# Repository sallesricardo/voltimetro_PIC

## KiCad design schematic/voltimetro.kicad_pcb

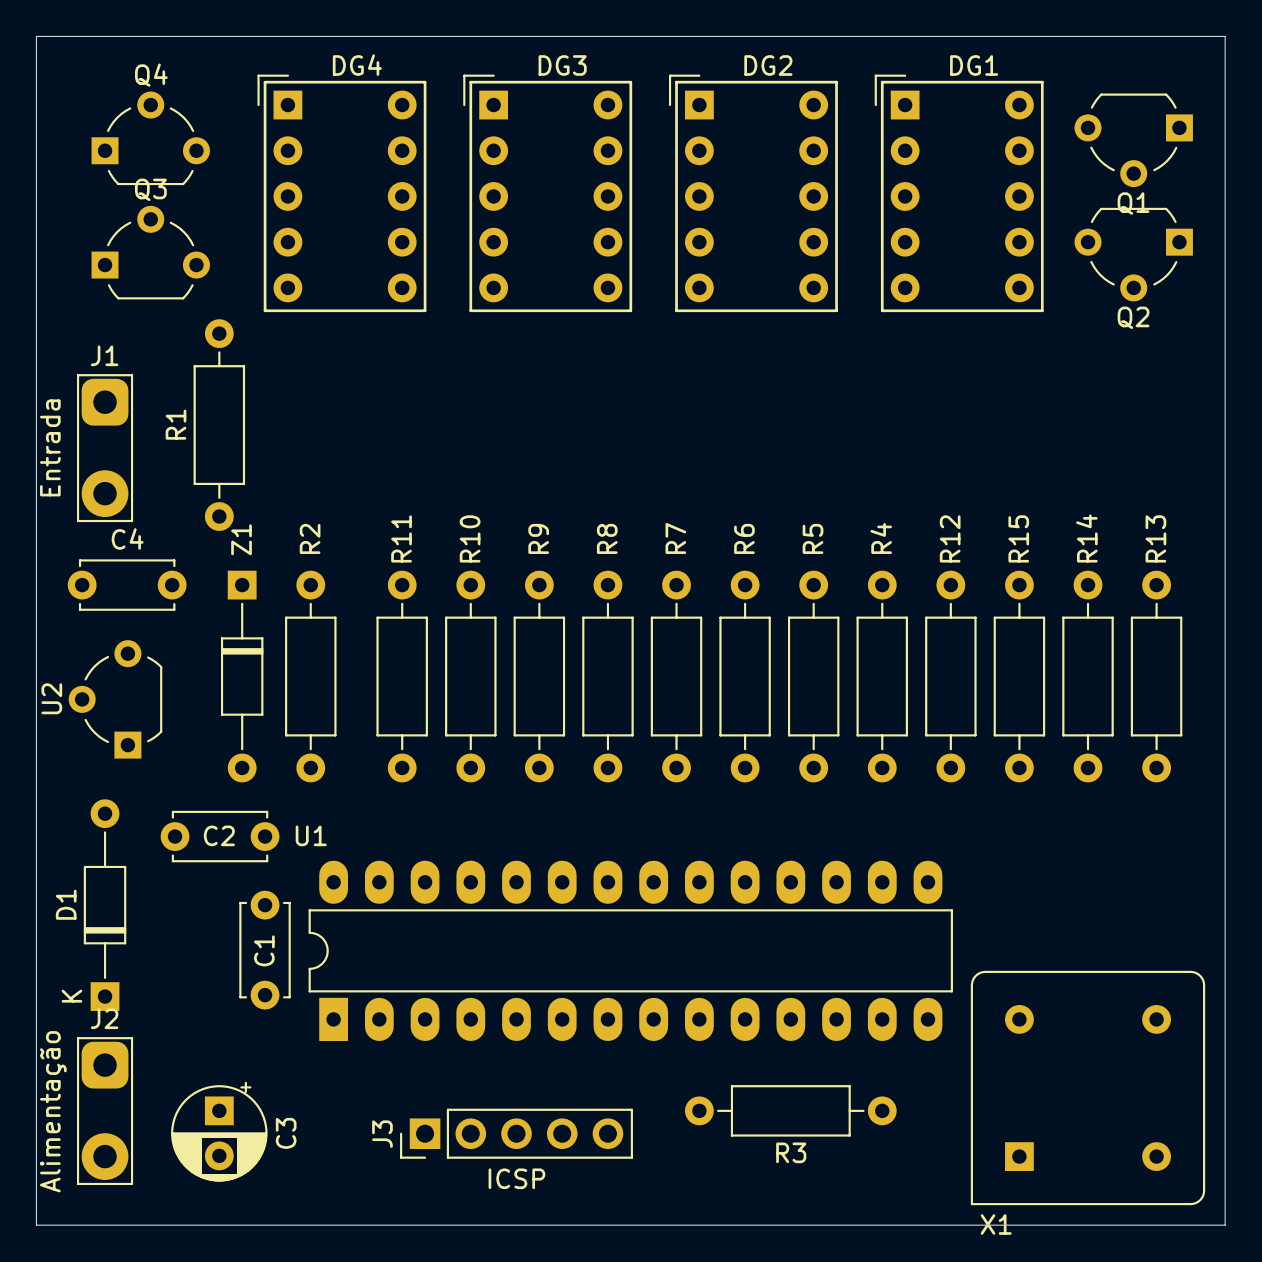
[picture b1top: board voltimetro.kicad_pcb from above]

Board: 2 copper layers, 66.0 x 66.0 mm, 35 parts (0 on the bottom side), 35 nets.

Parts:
C1, C2, C4: 100nF; C_Disc_D5.0mm_W2.5mm_P5.00mm
C3: 10uF; CP_Radial_D5.0mm_P2.50mm
D1: 1N4148; D_DO-35_SOD27_P10.16mm_Horizontal
DG1: Digito 1; 7Seg
DG2: Digito 2; 7Seg
DG3: Digito 3; 7Seg
DG4: Digito 4; 7Seg
J1: Entrada; TestPoint_2Pads_Pitch5.08mm_Drill1.3mm
J2: Alimentação; TestPoint_2Pads_Pitch5.08mm_Drill1.3mm
J3: ICSP; PinHeader_1x05_P2.54mm_Vertical
Q1, Q2, Q3, Q4: 2N2222A; TO-92_Wide
R1: 270K; R_Axial_DIN0207_L6.3mm_D2.5mm_P10.16mm_Horizontal
R2: 47k; R_Axial_DIN0207_L6.3mm_D2.5mm_P10.16mm_Horizontal
R3: 10K; R_Axial_DIN0207_L6.3mm_D2.5mm_P10.16mm_Horizontal
R4, R5, R6, R7, R8, R9, R10, R11: 220R; R_Axial_DIN0207_L6.3mm_D2.5mm_P10.16mm_Horizontal
R12, R13, R14, R15: 1K; R_Axial_DIN0207_L6.3mm_D2.5mm_P10.16mm_Horizontal
U1: PIC16F873A-I_SP; DIP-28_W7.62mm_LongPads
U2: 78L05; TO-92_Wide
X1: 10 MHz; Oscillator_DIP-8
Z1: 5,1V; D_DO-35_SOD27_P10.16mm_Horizontal

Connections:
+5V: C1.1, C3.1, D1.1, J2.1, J3.2, R3.1, U1.20, X1.8
GND: C1.2, C2.2, C3.2, C4.2, J1.2, J2.2, J3.3, Q1.1, Q2.1, Q3.1, Q4.1, R2.2, U1.8, U1.19, U2.2, X1.4, Z1.2
unnamed: C2.1, R1.1, R2.1, U1.2, Z1.1
unnamed: C4.1, J1.1, R1.2, U2.3
unnamed: D1.2, U2.1
unnamed: DG1.1, DG2.1, DG3.1, DG4.1, R8.1
unnamed: DG1.2, DG2.2, DG3.2, DG4.2, R7.1
unnamed: DG1.3, DG1.8, Q1.3
unnamed: DG1.4, DG2.4, DG3.4, DG4.4, R6.1
unnamed: DG1.5, DG2.5, DG3.5, DG4.5, R11.1
unnamed: DG1.6, DG2.6, DG3.6, DG4.6, R5.1
unnamed: DG1.7, DG2.7, DG3.7, DG4.7, R4.1
unnamed: DG1.9, DG2.9, DG3.9, DG4.9, R9.1
unnamed: DG1.10, DG2.10, DG3.10, DG4.10, R10.1
unnamed: DG2.3, DG2.8, Q2.3
unnamed: DG3.3, DG3.8, Q3.3
unnamed: DG4.3, DG4.8, Q4.3
unnamed: J3.1, R3.2, U1.1
unnamed: J3.4, R11.2, U1.28
unnamed: J3.5, R10.2, U1.27
unnamed: Q1.2, R12.1
unnamed: Q2.2, R15.1
unnamed: Q3.2, R14.1
unnamed: Q4.2, R13.1
unnamed: R4.2, U1.21
unnamed: R5.2, U1.22
unnamed: R6.2, U1.23
unnamed: R7.2, U1.24
unnamed: R8.2, U1.25
unnamed: R9.2, U1.26
unnamed: R12.2, U1.14
unnamed: R13.2, U1.11
unnamed: R14.2, U1.12
unnamed: R15.2, U1.13
unnamed: U1.9, X1.5

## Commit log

2019-10-07 Medição de tensão
2019-10-07 Update .gitignore
    Resolvendo merge
2020-02-10 Reorganização dos arquivos. Adicionando os arquivos do esquema.
2020-02-10 Remoção dos arquivos movidos no commit anterior
